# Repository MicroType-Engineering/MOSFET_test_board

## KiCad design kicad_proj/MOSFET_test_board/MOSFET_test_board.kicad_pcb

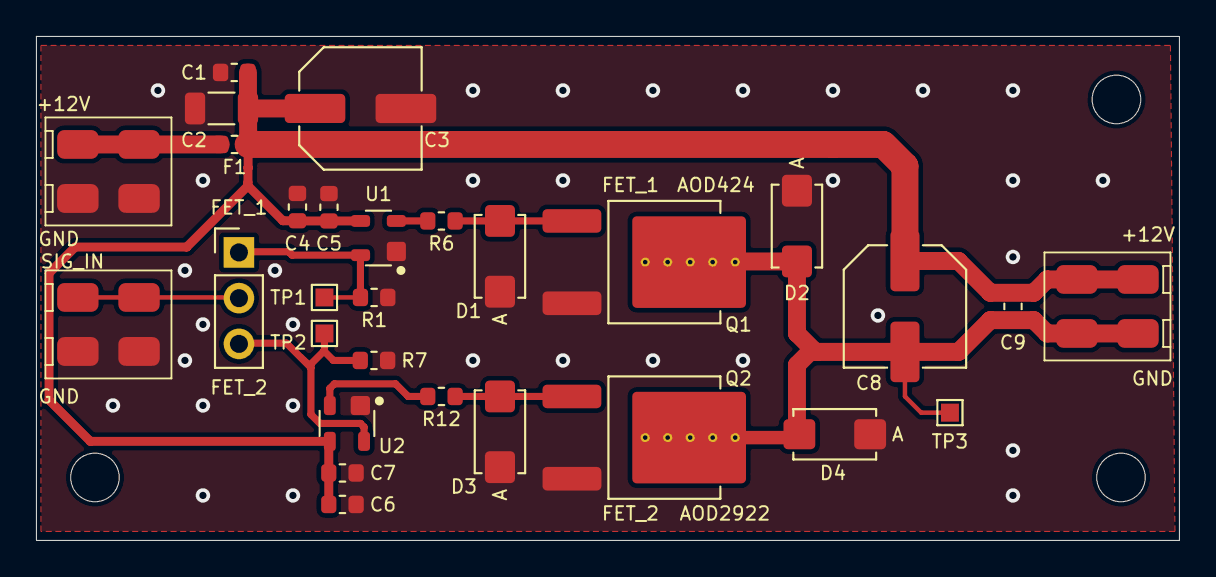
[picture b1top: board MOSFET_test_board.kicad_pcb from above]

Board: 2 copper layers, 63.5 x 28.0 mm, 29 parts (0 on the bottom side), 11 nets.

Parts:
C1, C5, C7, C9: CL10B104KC8NNNC; CAPACITOR_0603N
C2: CL31B105KCHNNNE; CAPACITOR_1206N
C3, C8: EMVE160ADA101MF55G; CAPAE660X550D720L265X65N
C4, C6: CL10A475KA8NQNC; CAPACITOR_0603N
D1, D2, D3, D4: SMAJ12A; DIODE_SMAN
F1: 0686F5000-01; FUSE_0603N
J1, J2, J3: 009296002202906
JP1: Jumper_NC_Dual; PinHeader_1x03_P2.54mm_Vertical
Q1: AOD424; DPAK3P457_994X240L165X76T538X492N
Q2: AOD2922; DPAK3P457_994X240L165X76T538X492N
R1, R7: RC0603JR-0710KL; RESISTOR_0603N
R6, R12: RC0603JR-0730RL; RESISTOR_0603N
TP1, TP2, TP3: TestPoint; TestPoint_Pad_1.0x1.0mm
U1, U2: MIC4416YM4-TR; SOT143-4P190_237X112L31X44N

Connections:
+12V: C1.1, C2.1, C3.1, C4.1, C5.1, C6.1, C7.1, C8.1, C9.1, F1.1, J3.2, U1.3, U2.3
/5V_SIG_IN: J2.1, JP1.2
/12V_IN: F1.2, J1.1
/CTRL_FET_1: JP1.1, R1.1, TP1.1, U1.4
/CTRL_FET_2: JP1.3, R7.1, TP2.1, U2.4
/DRAIN_FET: C8.2, C9.2, D2.C, D4.C, J3.1, Q1.4, Q2.4, TP3.1
GND: C1.2, C2.2, C3.2, C4.2, C5.2, C6.2, C7.2, D1.A, D2.A, D3.A, D4.A, J1.2, J2.2, Q1.3, Q2.3, R1.2, R7.2, U1.1, U2.1
unnamed: D1.C, Q1.1, R6.1
unnamed: D3.C, Q2.1, R12.1
unnamed: R6.2, U1.2
unnamed: R12.2, U2.2

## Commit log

2021-01-11 Finishes initial schematic
2021-01-13 Getting ready to swap to external square wave input
2021-01-18 Fab outputs
2021-09-20 Adds kibot test files
2021-09-20 Moves dev files to correct spot
